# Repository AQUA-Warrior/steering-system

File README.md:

## Custom Steering + Throttle/Brake System & Devboard

> *If You Want Total Control, You Have To Make It Yourself*

### Project Overview:
A custom, embedded hardware project to make my very own sim racing steering wheel and pedal systems. The project is powered by the STM32F732RET6 chip, using hall effect sensors for measuring inputs of the steering, throttle, and braking.

### Purpose Of The Project:
I started making this project knowing basically nothing about communication protocols or chip architectures. Instead of buying adapters that are already made for you. I wanted to make the entire system myself to learn and expand my knowledge, and create my very own sim racing setup. By designing this myself, I learned the strengths and weaknesses of communication protocols and which ones were best for which purpose. I wired up all the unused GPIO pins on the chip to connectors so that I would not just be locked down to the steering project, but instead, I can use it as a general purpose devboard for any future embedded hardware project I want to do.

### The Repository Contains:
- KiCad schematics and PCB's for the devboard and AS5047P adapter board.
- STM32CubeMX pinouts for the devboard.
- This repository contains firmware in the STM32/ folder

### Main Board Hardware:
- **Chip:** STM32F732RET6 (64-pin)
- **Power:** 5V VBUS from the USB-C, regulated to 3V3 using an AP2112k

### Main Board Design:
- 2 Layer PCB
- Minimum component size of 0603 used
- Two mounting holes (One on top right, One on bottom left)
- GND Zone on front copper
- 3V3 Zone on back copper

### AS5047P Adapter Board Design:
- 1 Layer PCB
- Minimum component size of 0603 used
- Two mounting holes (One on top right, One on bottom left)
- GND Zone on front copper

## Visuals
### Main Board Schematic:

### Main Board PCB:

### Main Board 3D View:

### AS5047P Adapter Board Schematic:

### AS5047P Adapter Board PCB:

### AS5047P Adapter Board 3D View:

## Bill Of Materials:

### Main Board:

| # | Reference | Qty | Value | Manufacturer | Manufacturer Part # | Footprint | Description | Price (1 Component) | Link |
|---:|---|---:|---|---|---|---|---|---:|---|
| 1 | F1 | 1 | Polyfuse | YAGEO | SMD0603B050TF | `Fuse:Fuse_0603_1608Metric_Pad1.05x0.95mm_HandSolder` | Resettable fuse, polymeric positive temperature coefficient | $0.36 | [DigiKey](https://www.digikey.ca/en/products/detail/yageo/SMD0603B050TF/15212923) |
| 2 | SW2 | 1 | SW_SPDT | Wurth Elektronik | 4.5E+11 | `450406020024:450406020024` | 9.0 × 3.5 mm, SPDT, ON-ON, Pitch 2.5 mm, Vertical type, SMT, T&R | $2.51 | [DigiKey](https://www.digikey.ca/en/products/detail/w%C3%BCrth-elektronik/450406020024/26249501?s=N4IgTCBcDaICwFYAMckDYliZuIC6AvkA) |
| 3 | D1 | 1 | RED | Wurth Elektronik | 150060RS75000 | `LED_SMD:LED_0603_1608Metric_Pad1.05x0.95mm_HandSolder` | Light emitting diode | $0.15 | [DigiKey](https://www.digikey.ca/en/products/detail/w%C3%BCrth-elektronik/150060RS75000/4489901) |
| 4 | U2 | 1 | USBLC6-2SC6 | STMicroelectronics | USBLC6-2SC6 | `Package_TO_SOT_SMD:SOT-23-6` | Very low capacitance ESD protection diode, 2 data-line, SOT-23-6 | $0.80 | [DigiKey](https://www.digikey.ca/en/products/detail/stmicroelectronics/USBLC6-2SC6/1040559) |
| 5 | U1 | 1 | STM32F732RET6 | STMicroelectronics | STM32F732RET6 | `Package_QFP:LQFP-64_10x10mm_P0.5mm` | STMicroelectronics Arm Cortex-M7 MCU, 512KB flash, 256KB RAM, 216 MHz, 1.7–3.6V, 50 GPIO, LQFP64 | $15.43 | [DigiKey](https://www.digikey.ca/en/products/detail/stmicroelectronics/STM32F732RET6/6621779?s=N4IgTCBcDaIMoBUCyBmMAxA7GgSgUQQDYQBdAXyA) |
| 6 | R4 | 1 | 100 | YAGEO | AC0603FR-07100RL | `Resistor_SMD:R_0603_1608Metric_Pad0.98x0.95mm_HandSolder` | Resistor | $0.24 | [DigiKey](https://www.digikey.ca/en/products/detail/yageo/AC0603FR-07100RL/5895735) |
| 7 | R2, R3 | 2 | 5.1k | YAGEO | AC0603FR-135K1L | `Resistor_SMD:R_0603_1608Metric_Pad0.98x0.95mm_HandSolder` | Resistor | $0.10 | [DigiKey](https://www.digikey.ca/en/products/detail/yageo/ac0603fr-135k1l/14008356) |
| 8 | R1 | 1 | 10k | YAGEO | RC0603FR-1010KL | `Resistor_SMD:R_0603_1608Metric_Pad0.98x0.95mm_HandSolder` | Resistor | $0.10 | [DigiKey](https://www.digikey.ca/en/products/detail/yageo/rc0603fr-1010kl/12756395) |
| 9 | FB1 | 1 | 120R | Murata Electronics | BLM18AG121SN1D | `Inductor_SMD:L_0603_1608Metric_Pad1.05x0.95mm_HandSolder` | Ferrite bead | $0.16 | [DigiKey](https://www.digikey.ca/en/products/detail/murata-electronics/BLM18AG121SN1D/584222?s=N4IgTCBcDaIEIBkCyBGAHAQQOIrCgygHIoAiIAugL5A) |
| 10 | C16 | 1 | 2.2uF | Murata Electronics | GRT188R61H225KE13D | `Capacitor_SMD:C_0603_1608Metric_Pad1.08x0.95mm_HandSolder` | Unpolarized capacitor | $0.20 | [DigiKey](https://www.digikey.ca/en/products/detail/murata-electronics/GRT188R61H225KE13D/5416754?s=N4IgTCBcDaIOICUAqBGAHGhA2FAJMYArANICiKAzACIgC6AvkA) |
| 11 | C11, C12 | 2 | 10pF | Murata Electronics | GRM1885C1H100JA01D | `Capacitor_SMD:C_0603_1608Metric_Pad1.08x0.95mm_HandSolder` | Unpolarized capacitor | $0.19 | [DigiKey](https://www.digikey.ca/en/products/detail/murata-electronics/grm1885c1h100ja01d/586930) |
| 12 | C8, C9, C14, C15 | 4 | 1uF | Murata Electronics | GRT188C8YA105KE13D | `Capacitor_SMD:C_0603_1608Metric_Pad1.08x0.95mm_HandSolder` | Unpolarized capacitor | $0.17 | [DigiKey](https://www.digikey.ca/en/products/detail/murata-electronics/GRT188C8YA105KE13D/5416719?s=N4IgTCBcDaIOICUAqBGAHGgwmgmgQRQAYBWAaQFEUBmAERAF0BfIA) |
| 13 | C7 | 1 | 10nF | Murata Electronics | GCM188R72A103KA37D | `Capacitor_SMD:C_0603_1608Metric_Pad1.08x0.95mm_HandSolder` | Unpolarized capacitor | $0.15 | [DigiKey](https://www.digikey.ca/en/products/detail/murata-electronics/GCM188R72A103KA37D/1641655) |
| 14 | C6, C17 | 2 | 10uF | Murata Electronics | GCJ21BR71A106KE01L | `Capacitor_SMD:C_0805_2012Metric_Pad1.18x1.45mm_HandSolder` | Unpolarized capacitor | $0.74 | [DigiKey](https://www.digikey.ca/en/products/detail/murata-electronics/GCJ21BR71A106KE01L/4903511) |
| 15 | C1, C2, C3, C4, C5, C10 | 6 | 100nF | Murata Electronics | GCM188L81H104KA57D | `Capacitor_SMD:C_0603_1608Metric_Pad1.08x0.95mm_HandSolder` | Unpolarized capacitor | $0.14 | [DigiKey](https://www.digikey.ca/en/products/detail/murata-electronics/GCM188L81H104KA57D/2591908?s=N4IgTCBcDaILIFcBOBDALigBAcQMJwEYAOIgGSIIAkCAGAFgGkBBAVgHYAREAXQF8g) |
| 16 | D2 | 1 | D_TVS | KYOCERA AVX | GG060305100N2P | `Diode_SMD:D_0603_1608Metric_Pad1.05x0.95mm_HandSolder` | Bidirectional transient-voltage-suppression diode | $0.45 | [DigiKey](https://www.digikey.ca/en/products/detail/kyocera-avx/GG060305100N2P/14552130?s=N4IgTCBcDaIOJwAwDZEGZEFYCMjEDkwAFEAXQF8g) |
| 17 | Y1 | 1 | 16MHz | Jauch Quartz | Q 16,0-JXS32-8-10/10-WA-LF | `Crystal:Crystal_SMD_3225-4Pin_3.2x2.5mm_HandSoldering` | Four pin crystal, GND on pins 2 and 4 | $0.61 | [DigiKey](https://www.digikey.ca/en/products/detail/jauch-quartz/Q-16-0-JXS32-8-10-10-WA-LF/8108046) |
| 18 | J1 | 1 | USB_C_Receptacle_USB2.0_14P | GCT | USB4085-GF-A | `Connector_USB:USB_C_Receptacle_GCT_USB4085` | USB 2.0-only 14P Type-C Receptacle connector | $0.91 | [DigiKey](https://www.digikey.ca/en/products/detail/gct/USB4085-GF-A/9859662?s=N4IgTCBcDaIKoGUBCAWADADgKwFoDiAYjgIIgC6AvkA) |
| 19 | U3 | 1 | AP2112K-3.3 | Diodes Incorporated | AP2112K-3.3TRG1 | `Package_TO_SOT_SMD:SOT-23-5` | 600mA low dropout linear regulator, with enable pin, 3.8–6V input voltage range, 3.3V fixed positive output, SOT-23-5 | $0.28 | [DigiKey](https://www.digikey.ca/en/products/detail/diodes-incorporated/AP2112K-3-3TRG1/4470746?s=N4IgTCBcDaIIIAcwEZlgNYFoDMA6bIAugL5A) |
| 20 | SW1 | 1 | SW_Push | Alps Alpine | SKSGACE010 | `ul_SKSGACE010:SKSGACE010_ALPS` | Push button switch, generic, two pins | $0.45 | [DigiKey](https://www.digikey.ca/en/products/detail/alps-alpine/SKSGACE010/19529157?s=N4IgTCBcDaIMoGk4HECCBhAogBgIzZAF0BfIA) |
| 21 | J8 | 1 | Conn_01x15_Socket | — | — | `Connector_PinHeader_2.54mm:PinHeader_1x15_P2.54mm_Vertical` | Generic connector, single row, 01x15, script generated | — | — |
| 22 | J7 | 1 | Conn_01x21_Socket | — | — | `Connector_PinHeader_2.54mm:PinHeader_1x21_P2.54mm_Vertical` | Generic connector, single row, 01x21, script generated | — | — |
| 23 | J6 | 1 | Conn_01x02_Socket USART2 | — | — | `Connector_PinHeader_2.54mm:PinHeader_1x02_P2.54mm_Vertical` | Generic connector, single row, 01x02, script generated | — | — |
| 24 | J4, J5 | 2 | Conn_01x03_Socket A1324LLHLT-T | — | — | `Connector_PinHeader_2.54mm:PinHeader_1x03_P2.54mm_Vertical` | Generic connector, single row, 01x03, script generated | — | — |
| 25 | J3 | 1 | Conn_01x06_Socket | — | — | `Connector_PinHeader_2.54mm:PinHeader_1x06_P2.54mm_Vertical` | Generic connector, single row, 01x06, script generated | — | — |
| 26 | J2 | 1 | Conn_01x04_Pin | — | — | `Connector_PinHeader_2.54mm:PinHeader_1x04_P2.54mm_Vertical` | Generic connector, single row, 01x04, script generated | — | — |

### AS5048 Adapter Board:

| # | Reference | Qty | Value | Manufacturer | Manufacturer Part # | Footprint | Description | Price (1 Component) | Link |
|---:|---|---:|---|---|---|---|---|---:|---|
| 1 | C1 | 1 | 100nF | Murata Electronics | GCM188L81H104KA57D | `Capacitor_SMD:C_0603_1608Metric_Pad1.08x0.95mm_HandSolder` | Unpolarized capacitor | $0.14 | [DigiKey](https://www.digikey.ca/en/products/detail/murata-electronics/GCM188L81H104KA57D/2591908?s=N4IgTCBcDaIOIGECyBGAHGgMmlAJFADACwDSAggKwDsAIiALoC%2BQA) |
| 2 | C2 | 1 | 1uF | Murata Electronics | GRT188C8YA105KE13D | `Capacitor_SMD:C_0603_1608Metric_Pad1.08x0.95mm_HandSolder` | Unpolarized capacitor | $0.17 | [DigiKey](https://www.digikey.ca/en/products/detail/murata-electronics/GRT188C8YA105KE13D/5416719?s=N4IgTCBcDaIOICUAqBGAHGgwmgmgQRQAYBWAaQFEUBmAERAF0BfIA) |
| 3 | J1 | 1 | Conn_01x07_Socket | — | — | `Connector_PinHeader_2.54mm:PinHeader_1x07_P2.54mm_Vertical` | Generic connector, single row, 01x07, script generated | — | — |
| 4 | U1 | 1 | AS5047P | Infineon Technologies | AS5047P-ATSM-TSSOP14 | `Package_SO:TSSOP-14_4.4x5mm_P0.65mm` | Magnetic position sensor, 14-bit, PWM output, SPI Interface, TSSOP-14 | $9.95$ | [DigiKey](https://www.digikey.ca/en/products/detail/infineon-technologies/AS5047P-ATSM-TSSOP14/29758312) |

### Linear Sensor:

| # | Reference | Qty | Value | Manufacturer | Manufacturer Part # | Footprint | Description | Price (1 Component) | Link |
|---:|---|---:|---|---|---|---|---|---:|---|
| 1 | — | 1 | — | Texas Instruments | DRV5055A1QLPG | — | SEN HALL EFFECT ANLG VOLT TO92-3 | $0.77 | [Digikey](https://www.digikey.ca/en/products/detail/texas-instruments/DRV5055A1QLPG) |

### Misc:

| # | Reference | Qty | Value | Manufacturer | Manufacturer Part # | Footprint | Description | Price (1 Component) | Link |
|---:|---|---:|---|---|---|---|---|---:|---|
| 1 | J1 | 1 | TSW-150-07-G-S | Samtec Inc. | TSW-150-07-G-S | — | 50-position, single-row, through-hole male pin header, 2.54 mm pitch | $4.27 | [DigiKey](https://www.digikey.ca/en/products/detail/samtec-inc/TSW-150-07-G-S/1101277) |
| 2 | — | 1 | 9042 | Radial Magnets, Inc. | 9042 | — | Neodymium N35 cylindrical magnet, 6 × 2.5 mm, diametrically magnetized | $0.63 | [DigiKey](https://www.digikey.ca/en/products/detail/radial-magnets-inc/9042/5640338) |
| 3 | — | 2 | 9027 | Radial Magnets, Inc. | 9027 | — | Neodymium N35SH cylindrical magnet, 4 × 2.5 mm, axially magnetized | $0.40 | [DigiKey](https://www.digikey.ca/en/products/detail/radial-magnets-inc/9027/5218822) |

### PCB:
| Item | Cost (USD) |
|---|---:|
| AS5048 Adapter Board PCB | $5.20 |
| AS5048 Adapter Board Stencil | $7.22 |
| Main Board PCB | $3.20 |
| Main Board PCB Stencil | $7.22 |

### Total: $83.79 USD
### Total (Including Tax): $94.69 USD

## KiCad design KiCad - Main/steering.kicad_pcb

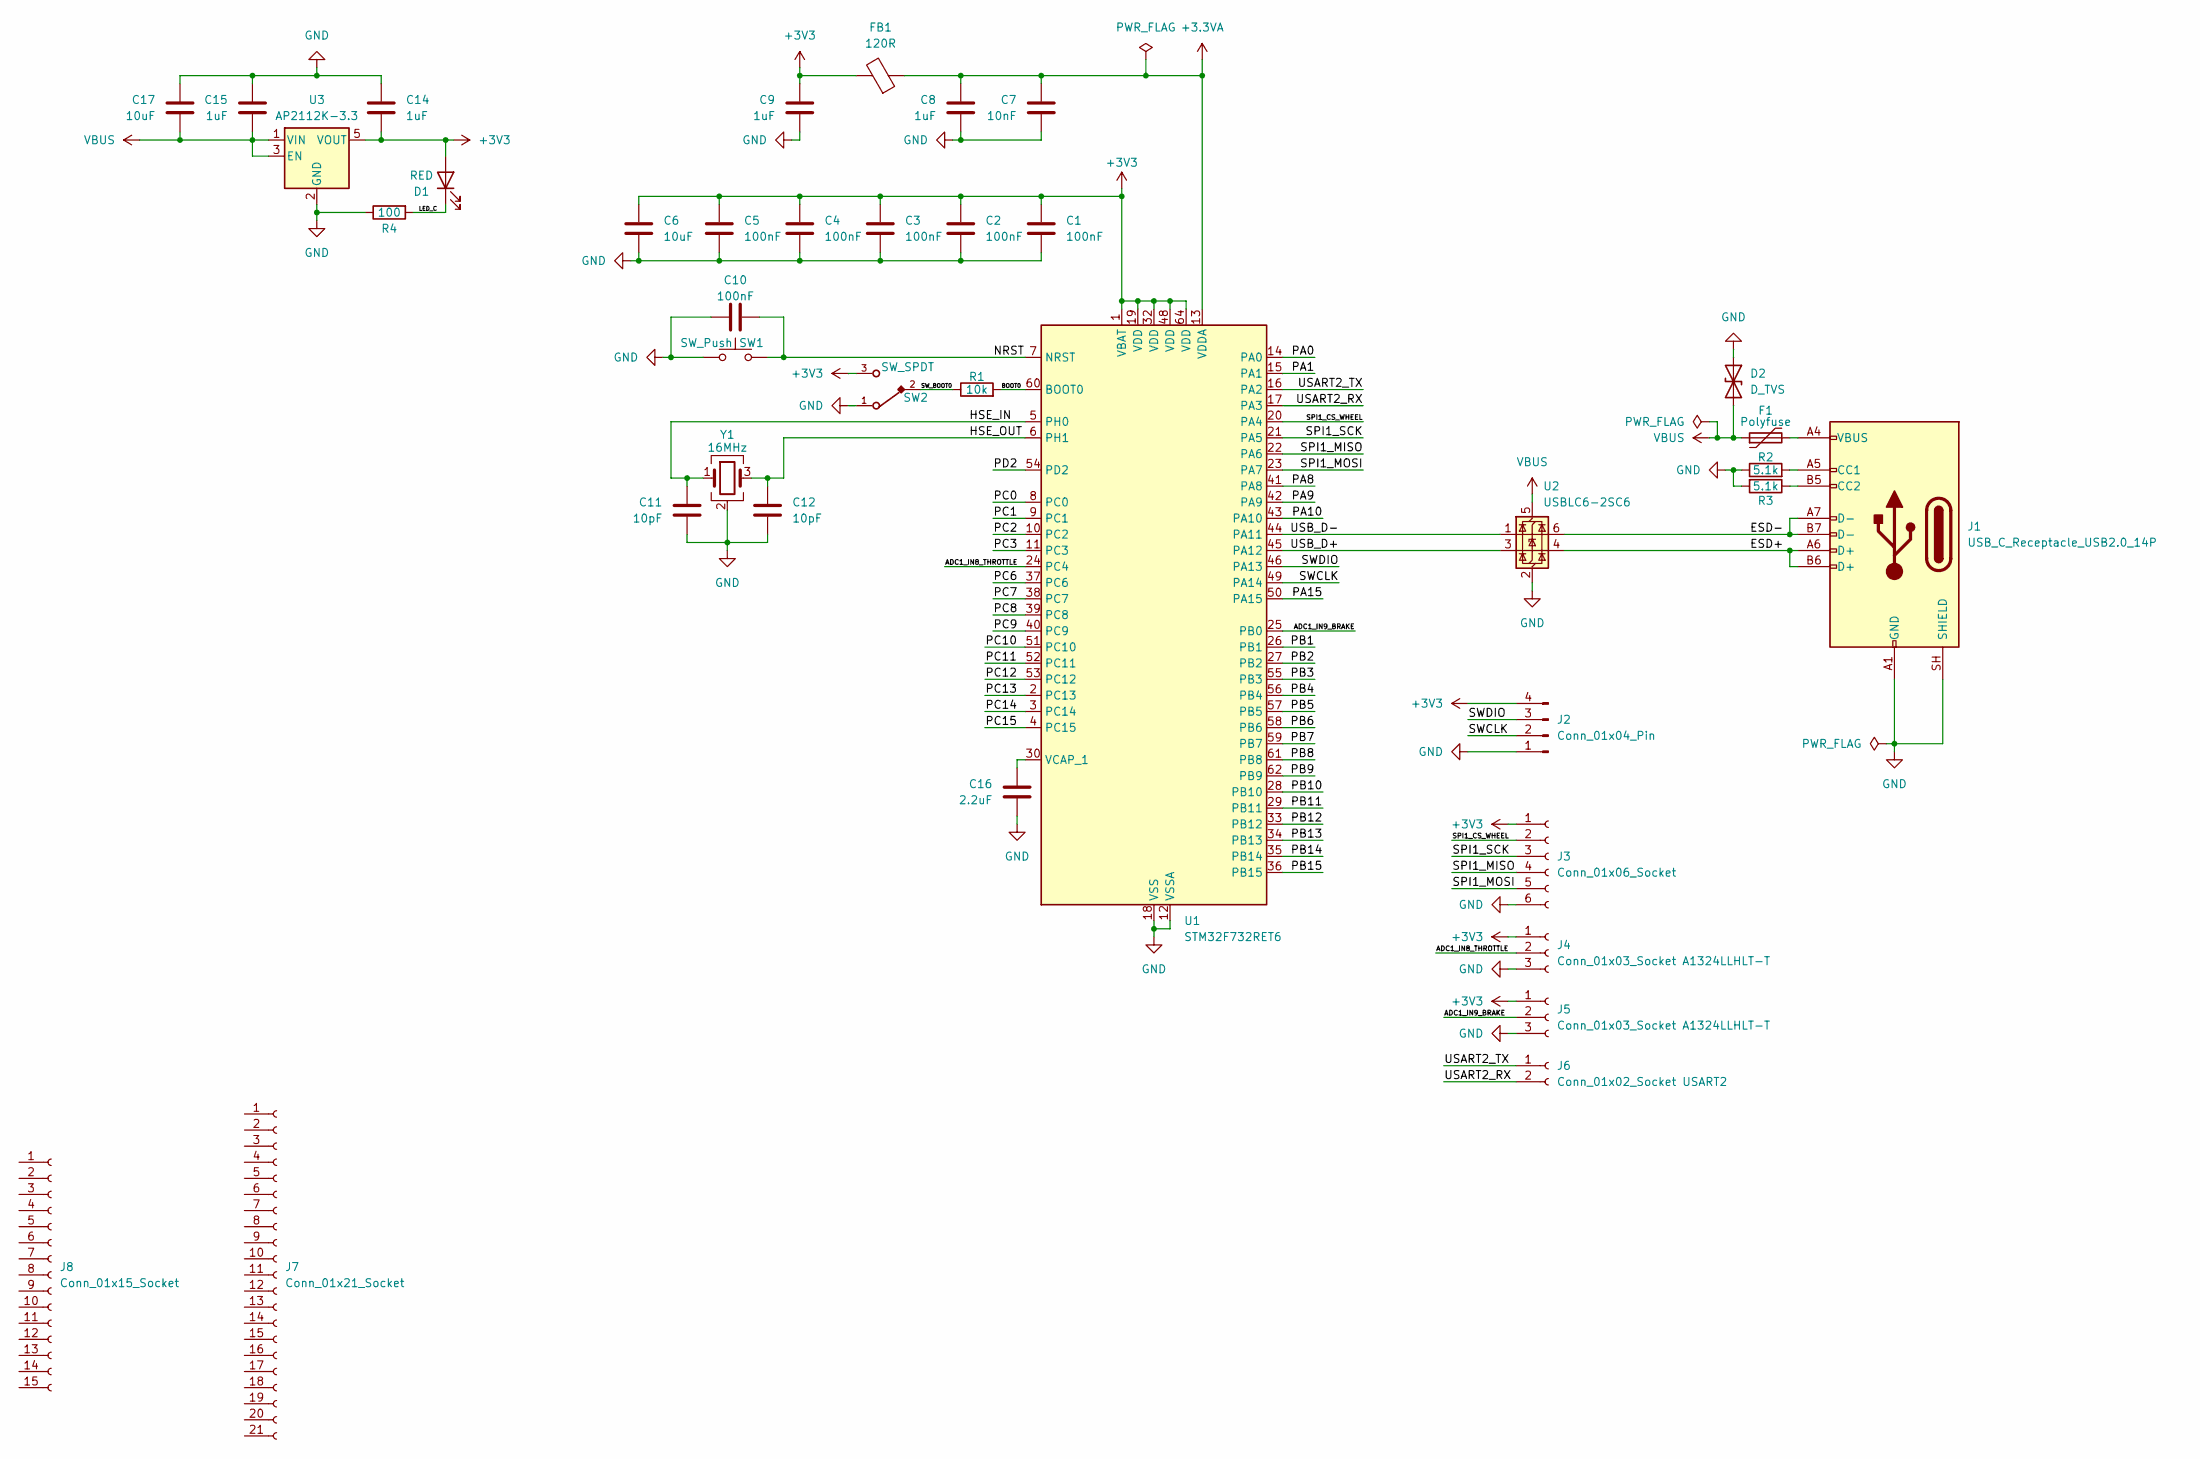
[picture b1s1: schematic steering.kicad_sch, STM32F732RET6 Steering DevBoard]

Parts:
C1, C2, C3, C4, C5, C10: 100nF; C_0603_1608Metric_Pad1.08x0.95mm_HandSolder
C6, C17: 10uF; C_0805_2012Metric_Pad1.18x1.45mm_HandSolder
C7: 10nF; C_0603_1608Metric_Pad1.08x0.95mm_HandSolder
C8, C9, C14, C15: 1uF; C_0603_1608Metric_Pad1.08x0.95mm_HandSolder
C11, C12: 10pF; C_0603_1608Metric_Pad1.08x0.95mm_HandSolder
C16: 2.2uF; C_0603_1608Metric_Pad1.08x0.95mm_HandSolder
D1: RED; LED_0603_1608Metric_Pad1.05x0.95mm_HandSolder
D2: D_TVS; D_0603_1608Metric_Pad1.05x0.95mm_HandSolder
F1: Polyfuse; Fuse_0603_1608Metric_Pad1.05x0.95mm_HandSolder
FB1: 120R; L_0603_1608Metric_Pad1.05x0.95mm_HandSolder
J1: USB_C_Receptacle_USB2.0_14P; USB_C_Receptacle_GCT_USB4085
J2: Conn_01x04_Pin; PinHeader_1x04_P2.54mm_Vertical
J3: Conn_01x06_Socket; PinHeader_1x06_P2.54mm_Vertical
J4, J5: Conn_01x03_Socket A1324LLHLT-T; PinHeader_1x03_P2.54mm_Vertical
J6: Conn_01x02_Socket USART2; PinHeader_1x02_P2.54mm_Vertical
J7: Conn_01x21_Socket; PinHeader_1x21_P2.54mm_Vertical
J8: Conn_01x15_Socket; PinHeader_1x15_P2.54mm_Vertical
R1: 10k; R_0603_1608Metric_Pad0.98x0.95mm_HandSolder
R2, R3: 5.1k; R_0603_1608Metric_Pad0.98x0.95mm_HandSolder
R4: 100; R_0603_1608Metric_Pad0.98x0.95mm_HandSolder
SW1: SW_Push; SKSGACE010_ALPS
SW2: SW_SPDT; 450406020024; DigiKey_Part_Number 732-450406020024CT-ND
U1: STM32F732RET6; LQFP-64_10x10mm_P0.5mm
U2: USBLC6-2SC6; SOT-23-6
U3: AP2112K-3.3; SOT-23-5
Y1: 16MHz; Crystal_SMD_3225-4Pin_3.2x2.5mm_HandSoldering

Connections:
+3.3VA: C7.1, C8.1, FB1.1, U1.13 (VDDA)
+3V3: C1.1, C2.1, C3.1, C4.1, C5.1, C6.1, C9.1, C14.2, D1.2 (A), FB1.2, J2.4, J3.1, J4.1, J5.1, SW2.3, U1.1 (VBAT), U1.19 (VDD), U1.32 (VDD), U1.48 (VDD), U1.64 (VDD), U3.5 (VOUT)
/ADC1_IN8_THROTTLE: J4.2, U1.24 (PC4)
/ADC1_IN9_BRAKE: J5.2, U1.25 (PB0)
/BOOT0: R1.2, U1.60 (BOOT0)
/ESD+: J1.A6 (D+), J1.B6 (D+), U2.4 (I/O2)
/ESD-: J1.A7 (D-), J1.B7 (D-), U2.6 (I/O1)
/HSE_IN: C11.2, U1.5 (PH0), Y1.1
/HSE_OUT: C12.1, U1.6 (PH1), Y1.3
/LED_C: D1.1 (K), R4.2
/NRST: C10.1, SW1.2, U1.7 (NRST)
/PA0: U1.14 (PA0)
/PA1: U1.15 (PA1)
/PA8: U1.41 (PA8)
/PA9: U1.42 (PA9)
/PA10: U1.43 (PA10)
/PA15: U1.50 (PA15)
/PB1: U1.26 (PB1)
/PB2: U1.27 (PB2)
/PB3: U1.55 (PB3)
/PB4: U1.56 (PB4)
/PB5: U1.57 (PB5)
/PB6: U1.58 (PB6)
/PB7: U1.59 (PB7)
/PB8: U1.61 (PB8)
/PB9: U1.62 (PB9)
/PB10: U1.28 (PB10)
/PB11: U1.29 (PB11)
/PB12: U1.33 (PB12)
/PB13: U1.34 (PB13)
/PB14: U1.35 (PB14)
/PB15: U1.36 (PB15)
/PC0: U1.8 (PC0)
/PC1: U1.9 (PC1)
/PC2: U1.10 (PC2)
/PC3: U1.11 (PC3)
/PC6: U1.37 (PC6)
/PC7: U1.38 (PC7)
/PC8: U1.39 (PC8)
/PC9: U1.40 (PC9)
/PC10: U1.51 (PC10)
/PC11: U1.52 (PC11)
/PC12: U1.53 (PC12)
/PC13: U1.2 (PC13)
/PC14: U1.3 (PC14)
/PC15: U1.4 (PC15)
/PD2: U1.54 (PD2)
/SPI1_CS_WHEEL: J3.2, U1.20 (PA4)
/SPI1_MISO: J3.4, U1.22 (PA6)
/SPI1_MOSI: J3.5, U1.23 (PA7)
/SPI1_SCK: J3.3, U1.21 (PA5)
/SWCLK: J2.2, U1.49 (PA14)
/SWDIO: J2.3, U1.46 (PA13)
/SW_BOOT0: R1.1, SW2.2
/USART2_RX: J6.2, U1.17 (PA3)
/USART2_TX: J6.1, U1.16 (PA2)
/USB_D+: U1.45 (PA12), U2.3 (I/O2)
/USB_D-: U1.44 (PA11), U2.1 (I/O1)
GND: C1.2, C2.2, C3.2, C4.2, C5.2, C6.2, C7.2, C8.2, C9.2, C10.2, C11.1, C12.2, C14.1, C15.2, C16.2, C17.2, D2.1 (A1), J1.A1 (GND), J1.A12 (GND), J1.B1 (GND), J1.B12 (GND), J1.SH (SHIELD), J2.1, J3.6, J4.3, J5.3, R2.1, R3.2, R4.1, SW1.1, SW2.1, U1.12 (VSSA), U1.18 (VSS), U1.31 (VSS), U1.47 (VSS), U1.63 (VSS), U2.2 (GND), U3.2 (GND), Y1.2 (G), Y1.4 (G)
unnamed: F1.2, J1.A4 (VBUS), J1.A9 (VBUS), J1.B4 (VBUS), J1.B9 (VBUS)
unnamed: J1.A5 (CC1), R2.2
unnamed: J1.B5 (CC2), R3.1
unnamed: C16.1, U1.30 (VCAP_1)
VBUS: C15.1, C17.1, D2.2 (A2), F1.1, U2.5 (VBUS), U3.1 (VIN), U3.3 (EN)

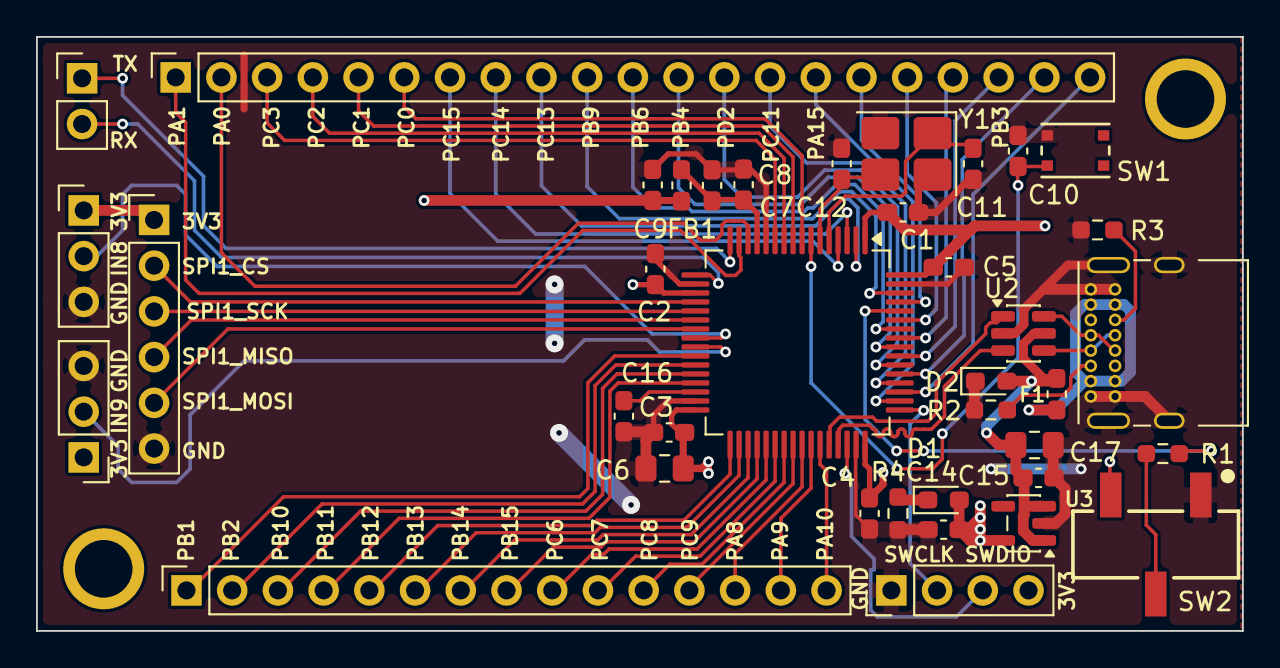
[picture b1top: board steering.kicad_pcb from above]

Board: 2 copper layers, 67.0 x 33.0 mm, 36 parts (0 on the bottom side), 28 nets.

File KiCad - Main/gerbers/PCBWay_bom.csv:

Designator,Quantity,Value,Footprint,Package,MPN,DNP,Mount_Type,Description,Link,Price,MF,MP,Sim.Pins,KiLib_Generator,DigiKey_Part_Number,SnapEDA_Link,Check_prices
"C1, C10, C2, C3, C4, C5",6,100nF,C_0603_1608Metric_Pad1.08x0.95mm_HandSolder,,,,smt,Unpolarized capacitor,https://www.digikey.com/en/products/detail/murata-electronic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,$0.14,Murata Electronics,GCM188L81H104KA57D,,,,,
"C11, C12",2,10pF,C_0603_1608Metric_Pad1.08x0.95mm_HandSolder,,,,smt,Unpolarized capacitor,https://www.digikey.com/en/products/detail/murata-electronic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,$0.11,Murata Electronics,GCM1555C1H100JA16D,,,,,
"C14, C15, C8, C9",4,1uF,C_0603_1608Metric_Pad1.08x0.95mm_HandSolder,,,,smt,Unpolarized capacitor,https://www.digikey.com/en/products/detail/murata-electronic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,$0.17,Murata Electronics,GRT188C8YA105KE13D,,,,,
C16,1,2.2uF,C_0603_1608Metric_Pad1.08x0.95mm_HandSolder,,,,smt,Unpolarized capacitor,https://www.digikey.com/en/products/detail/murata-electronic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,$0.2,Murata Electronics,GRT188R61H225KE13D,,,,,
"C17, C6",2,10uF,C_0805_2012Metric_Pad1.18x1.45mm_HandSolder,,,,smt,Unpolarized capacitor,https://www.digikey.ca/en/products/detail/murata-electronics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,$0.74,Murata Electronics,GCJ21BR71A106KE01L,,,,,
C7,1,10nF,C_0603_1608Metric_Pad1.08x0.95mm_HandSolder,,,,smt,Unpolarized capacitor,https://www.digikey.ca/en/products/detail/murata-electronics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,$0.15,Murata Electronics,GCM188R72A103KA37D,,,,,
D1,1,RED,LED_0603_1608Metric_Pad1.05x0.95mm_HandSolder,,,,smt,Light emitting diode,https://www.digikey.com/en/products/detail/w%C3%BCrth-elektr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,$0.15,Wurth Elektronik,150060RS75000,1=K 2=A,,,,
D2,1,D_TVS,D_0603_1608Metric_Pad1.05x0.95mm_HandSolder,,,,smt,Bidirectional transient-voltage-suppression diode,https://www.digikey.ca/en/products/detail/kyocera-avx/GG0603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,$0.45,KYOCERA AVX,GG060305100N2P,,,,,
F1,1,Polyfuse,Fuse_0603_1608Metric_Pad1.05x0.95mm_HandSolder,,,,smt,"Resettable fuse, polymeric positive temperature coefficient",https://www.digikey.ca/en/products/detail/yageo/SMD0603B050T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,$0.36,YAGEO,SMD0603B050TF,,,,,
FB1,1,120R,L_0603_1608Metric_Pad1.05x0.95mm_HandSolder,,,,smt,Ferrite bead,https://www.digikey.ca/en/products/detail/murata-electronics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,$0.16,Murata Electronics,BLM18AG121SN1D,,,,,
J1,1,USB_C_Receptacle_USB2.0_14P,USB_C_Receptacle_GCT_USB4085,,,,tht,USB 2.0-only 14P Type-C Receptacle connector,https://www.digikey.com/en/products/detail/gct/USB4085-GF-A/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,$0.91,GCT,USB4085-GF-A,,,,,
J2,1,Conn_01x04_Pin,PinHeader_1x04_P2.54mm_Vertical,,,,tht,"Generic connector, single row, 01x04, script generated",,,,,,,,,
J3,1,Conn_01x06_Socket,PinHeader_1x06_P2.54mm_Vertical,,,,tht,"Generic connector, single row, 01x06, script generated",,,,,,,,,
"J4, J5",2,Conn_01x03_Socket A1324LLHLT-T,PinHeader_1x03_P2.54mm_Vertical,,,,tht,"Generic connector, single row, 01x03, script generated",,,,,,,,,
J6,1,Conn_01x02_Socket USART2,PinHeader_1x02_P2.54mm_Vertical,,,,tht,"Generic connector, single row, 01x02, script generated",,,,,,,,,
R1,1,10k,R_0603_1608Metric_Pad0.98x0.95mm_HandSolder,,,,smt,Resistor,https://www.digikey.com/en/products/detail/panasonic-industr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,$0.1,Panasonic Industry,ERJ-3EKF1002V,,,,,
"R2, R3",2,5.1k,R_0603_1608Metric_Pad0.98x0.95mm_HandSolder,,,,smt,Resistor,https://www.digikey.com/en/products/detail/panasonic-industr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,$0.15,Panasonic Industry,ERJ-3EKF5101V,,,,,
R4,1,100,R_0603_1608Metric_Pad0.98x0.95mm_HandSolder,,,,smt,Resistor,https://www.digikey.ca/en/products/detail/panasonic-industry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,$0.24,Panasonic Industry,ERJ-PA3F1000V,,,,,
SW1,1,SW_Push,SKSGACE010_ALPS,,,,smt,"Push button switch, generic, two pins",https://www.digikey.com/en/products/detail/alps-alpine/SKSGA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,$0.45,Alps Alpine,SKSGACE010,,,,,
SW2,1,SW_SPDT,450406020024,None,,,smt,"9.0*3.5 mm, SPDT, ON-ON, Pitch 2.5mm, Vertical type, SMT, T&R",https://www.digikey.com/en/products/detail/w%C3%BCrth-elektr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,$2.51,Wurth Elektronik,450406020024,,,732-450406020024CT-ND,https://www.snapeda.com/parts/450406020024/Wurth+Electronics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,https://www.snapeda.com/parts/450406020024/Wurth+Electronics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
U1,1,STM32F732RET6,LQFP-64_10x10mm_P0.5mm,,,,smt,"STMicroelectronics Arm Cortex-M7 MCU, 512KB flash, 256KB RAM, 216 MHz, 1.7-3.6V, 50 GPIO, LQFP64",https://www.digikey.com/en/products/detail/stmicroelectronic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,$15.43,STMicroelectronics,STM32F732RET6,,,,,
U2,1,USBLC6-2SC6,SOT-23-6,,,,smt,"Very low capacitance ESD protection diode, 2 data-line, SOT-23-6",https://www.digikey.com/en/products/detail/stmicroelectronic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,$0.54,STMicroelectronics,USBLC6-2SC6,,,,,
U3,1,AP2112K-3.3,SOT-23-5,,,,smt,"600mA low dropout linear regulator, with enable pin, 3.8V-6V input voltage range, 3.3V fixed positive output, SOT-23-5",https://www.digikey.com/en/products/detail/diodes-incorporat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,$0.28,Diodes Incorporated,AP2112K-3.3TRG1,,,,,
Y1,1,16MHz,Crystal_SMD_3225-4Pin_3.2x2.5mm_HandSoldering,,,,smt,"Four pin crystal, GND on pins 2 and 4",https://www.digikey.com/en/products/detail/jauch-quartz/Q-16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,$0.61,Jauch Quartz,"Q 16,0-JXS32-8-10/10-WA-LF",,,,,

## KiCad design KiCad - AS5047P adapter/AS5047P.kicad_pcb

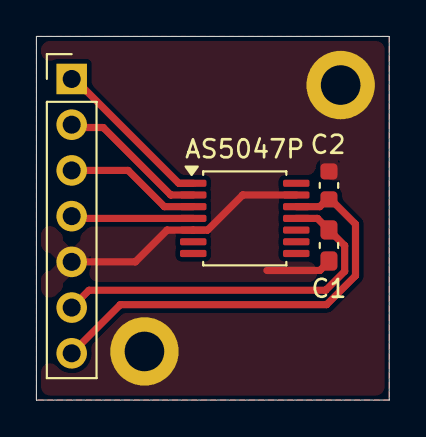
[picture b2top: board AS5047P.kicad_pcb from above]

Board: 2 copper layers, 19.6 x 20.2 mm, 4 parts (0 on the bottom side), 7 nets.

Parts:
AS5047P: AS5048A; TSSOP-14_4.4x5mm_P0.65mm
C1: 100nF; C_0603_1608Metric_Pad1.08x0.95mm_HandSolder
C2: 1uF; C_0603_1608Metric
J1: Conn_01x07_Socket; PinHeader_1x07_P2.54mm_Vertical

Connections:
+3V3: AS5047P.12 (VDD3V), C2.1, J1.7
+5V: AS5047P.11 (VDD5V), C1.2, J1.6
/CLK: AS5047P.2 (CLK), J1.2
/CS: AS5047P.1 (~CSn), J1.1
/MISO: AS5047P.3 (MISO), J1.3
/MOSI: AS5047P.4 (MOSI), J1.4
GND: AS5047P.5 (TEST), AS5047P.13 (GND), C1.1, C2.2, J1.5

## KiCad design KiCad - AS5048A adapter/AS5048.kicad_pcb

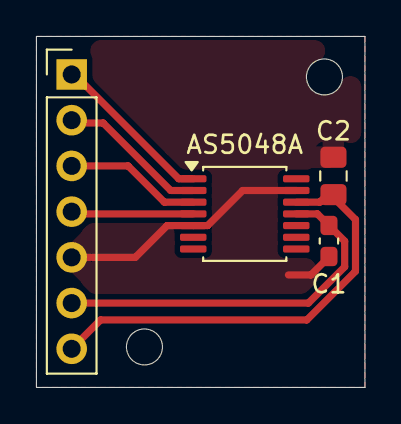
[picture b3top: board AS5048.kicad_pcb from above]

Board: 2 copper layers, 18.2 x 19.5 mm, 4 parts (0 on the bottom side), 7 nets.

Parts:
AS5048A: AS5048A; TSSOP-14_4.4x5mm_P0.65mm
C1: 100nF; C_0603_1608Metric_Pad1.08x0.95mm_HandSolder
C2: 10uF; C_0805_2012Metric_Pad1.18x1.45mm_HandSolder
J1: Conn_01x07_Socket; PinHeader_1x07_P2.54mm_Vertical

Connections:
+3V3: AS5048A.12 (VDD3V), C2.1, J1.7
+5V: AS5048A.11 (VDD5V), C1.2, J1.6
/CLK: AS5048A.2 (CLK), J1.2
/CS: AS5048A.1 (~CSn), J1.1
/MISO: AS5048A.3 (MISO), J1.3
/MOSI: AS5048A.4 (MOSI), J1.4
GND: AS5048A.5 (TEST), AS5048A.13 (GND), C1.1, C2.2, J1.5

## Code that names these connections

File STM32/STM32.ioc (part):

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Mcu.Name=STM32F732RETx
Mcu.Package=LQFP64
Mcu.UserName=STM32F732RETx
PA11.Mode=Device_Only
PA11.Signal=USB_OTG_FS_DM
PA12.Mode=Device_Only
PA12.Signal=USB_OTG_FS_DP
PA13.Mode=Serial_Wire
PA13.Signal=SYS_JTMS-SWDIO
PA14.Mode=Serial_Wire
PA14.Signal=SYS_JTCK-SWCLK
PA4.Signal=GPIO_Output
PA5.Mode=Full_Duplex_Master
PA5.Signal=SPI1_SCK
PA6.Mode=Full_Duplex_Master
PA6.Signal=SPI1_MISO
PA7.Mode=Full_Duplex_Master
PA7.Signal=SPI1_MOSI
PA9.Mode=Activate_VBUS
PA9.Signal=USB_OTG_FS_VBUS
PB0.Signal=ADCx_IN8
PC4.Signal=ADCx_IN14
PH0-OSC_IN.Mode=HSE-External-Oscillator
PH0-OSC_IN.Signal=RCC_OSC_IN
PH1-OSC_OUT.Mode=HSE-External-Oscillator
PH1-OSC_OUT.Signal=RCC_OSC_OUT
RCC.HSE_VALUE=16000000
board=custom

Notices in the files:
KiCad - AS5047P adapter/AS5047P.kicad_pcb:
© AQUAWarrior
